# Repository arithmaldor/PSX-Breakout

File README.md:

# Copyright and Disclaimer
Copyright: Jacob Proctor

This documentation describes Open Hardware and is licensed under the
CERN OHL v. 1.2.

You may redistribute and modify this documentation under the terms of the
CERN OHL v.1.2. (http://ohwr.org/cernohl). This documentation is distributed
WITHOUT ANY EXPRESS OR IMPLIED WARRANTY, INCLUDING OF
MERCHANTABILITY, SATISFACTORY QUALITY AND FITNESS FOR A
PARTICULAR PURPOSE. Please see the CERN OHL v.1.2 for applicable
conditions

# PSX Breakout
Breaks out all of the signals from the PSX AV out so you can easily access them. 

# Operation
Plug in and go.

## HD15 SYNC Selector 
Located on the back left of the board, this switch determines which signal goes to the HD15 port - CVBS or LUMA.

# Parts
Refer to BOM.csv for all components. For the support leg, use any appropriately long brass/metal m3 standoff/pillar and screw a rubber foot to the bottom. Solder a 5mm spring clamp to the bottom of the board to adjust the height.
For the phat PS3, standoffs may need to be screwed into each other (stacked) to reach the needed height.

# Case
The incredible [Magic Trashman](https://twitter.com/MagicTrashman) was kind enough to design 3D printable cases for both my Nintendo and PSX breakouts. They are under the same license as the PCB and are free to use, but if you order through thingiverse you can leave him a nice tip. Current designs fit the height of the original PS1 and the original SNES, but can be easily adjusted for height if you have some basic 3D design skills. They are held together with 2x 14mm M3 machine screws.
Pictures: https://t.co/ojJ8epfZXH?amp=1
Thingiverse: https://t.co/7dF171BqaF?amp=1
Bonus: If you plug the Nintendo/Sony connector into the console and screw the PCB into the bottom of the case, it makes it a lot easier to solder the connector to the board as it is held in place.

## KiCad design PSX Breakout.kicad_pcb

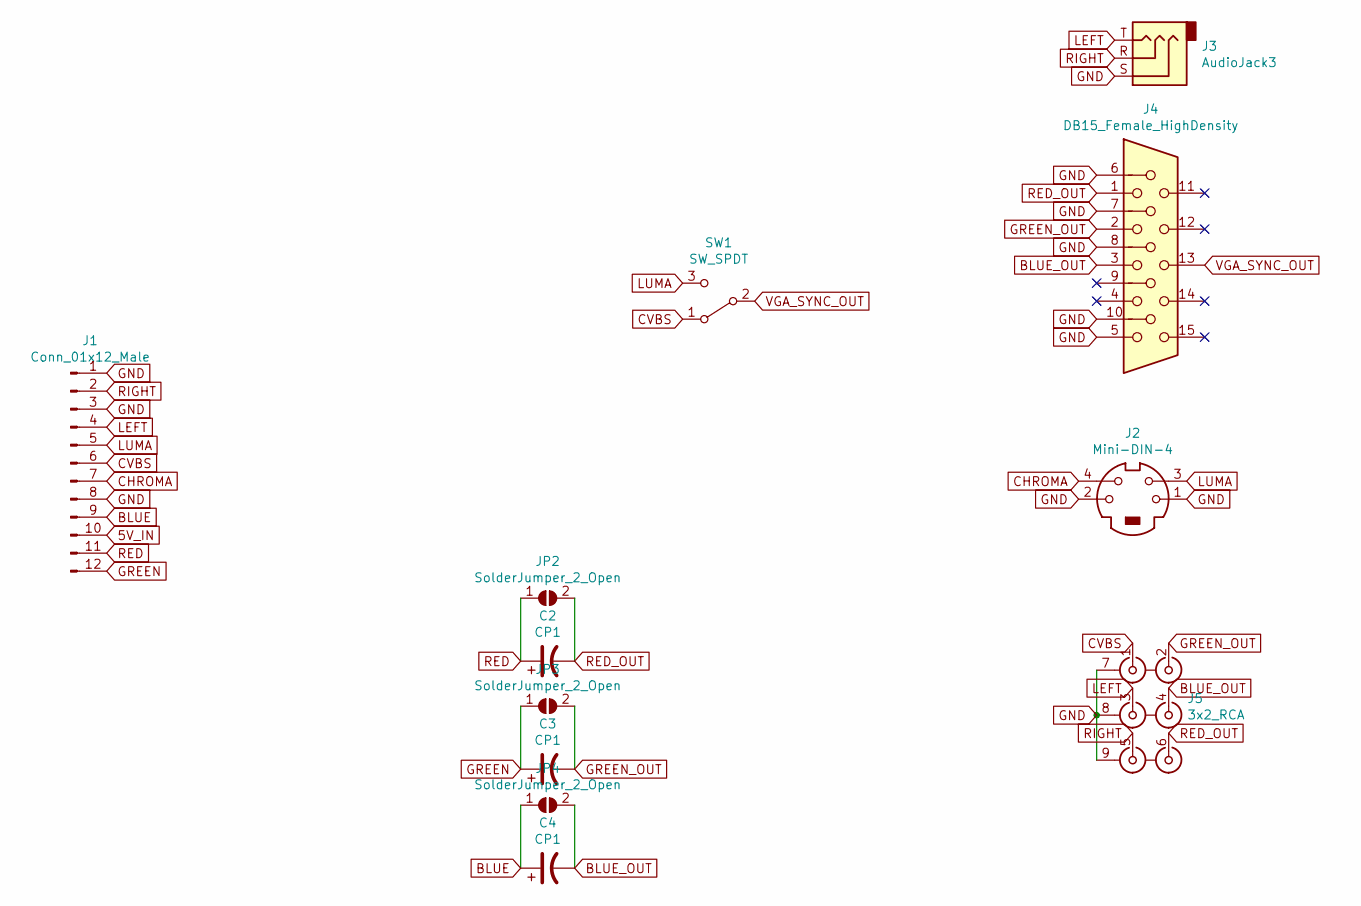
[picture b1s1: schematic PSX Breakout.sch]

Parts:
C2, C3, C4: CP1; CP_Elec_10x10
J1: Conn_01x12_Male; PSX_AV
J2: Mini-DIN-4; CUI_MD-40SG
J3: AudioJack3; CUI_SJ1-3533NG
J4: DB15_Female_HighDensity; VGA
J5: 3x2_RCA
JP2, JP3, JP4: SolderJumper_2_Open; SolderJumper-2_P1.3mm_Open_TrianglePad1.0x1.5mm
SW1: SW_SPDT; C&K_SPDT

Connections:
5V_IN: J1.10
BLUE: C4.1, J1.9, JP4.1 (A)
BLUE_OUT: C4.2, J4.3, J5.4 (INGRN), JP4.2 (B)
CHROMA: J1.7, J2.4
CVBS: J1.6, J5.1 (INSYN), SW1.1 (A)
GND: J1.1, J1.3, J1.8, J2.1, J2.2, J3.S, J4.0, J4.5, J4.6, J4.7, J4.8, J4.10, J5.7 (GND), J5.8 (GND), J5.9 (GND), SW1.S
GREEN: C3.1, J1.12, JP3.1 (A)
GREEN_OUT: C3.2, J4.2, J5.2 (INRED), JP3.2 (B)
LEFT: J1.4, J3.T, J5.3 (INLAU)
LUMA: J1.5, J2.3, SW1.3 (C)
RED: C2.1, J1.11, JP2.1 (A)
RED_OUT: C2.2, J4.1, J5.6 (INBLU), JP2.2 (B)
RIGHT: J1.2, J3.R, J5.5 (INRAU)
VGA_SYNC_OUT: J4.13, SW1.2 (B)

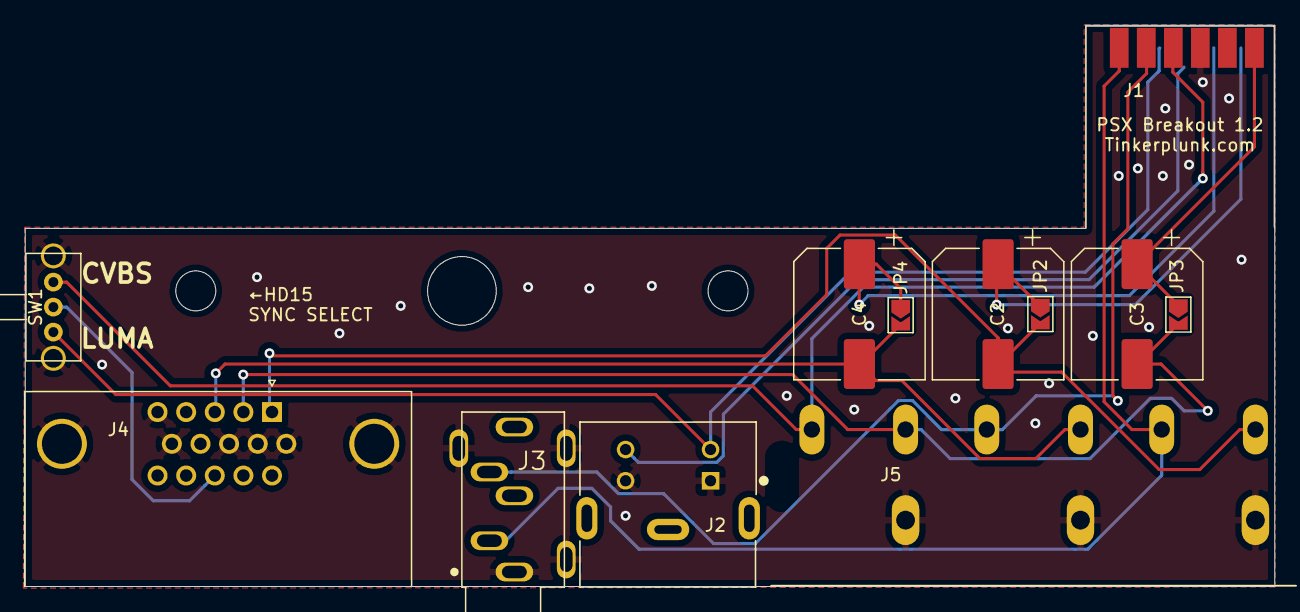
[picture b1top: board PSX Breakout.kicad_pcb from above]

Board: 2 copper layers, 100.0 x 44.9 mm, 12 parts (0 on the bottom side), 13 nets.

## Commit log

2019-06-09 Updated Case Gerbers
2019-06-09 Case edit, renders
    moved the case back a bit behind the RCA jacks to give space, added renders that include the case.
2019-06-11 Fixing Merging Error
    Updated Case, moved connector, generated gerbers
2019-06-13 Changed headphone jack footprint
    Added pins to the headphone jack footprint so it is compatible with all SJ1-353x-n, ng, and ns series jacks.
2019-06-13 Completed BOM
2019-06-16 Big Changes
    Moved the csync selector switch to the right in order to move the hd15 connector back to the right position. Fixed hd15 footprint, moved screw holes and updated case with new screw holes and input la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
2019-06-17 Updated BOM
2019-06-17 Fixed Gerbers, added footprints
    Updated gerbers, and added all footprints used on this board to the PSX_BREAKOUT.Pretty folder.
2019-06-18 Added Hardware BOM
    Added hardware BOM and diagram, updated readme.
2019-06-25 Fixed s-video and headphone footprint, added support hole
2019-07-03 no change
2019-07-06 Updated to 1.2
    Removed sync stripper, shrunk board, added switch to select sync source of HD15 port only.
2019-07-31 Changed s-video footprint
2019-07-31 Update fp-info-cache
2019-08-02 Finishing Touches
2019-09-09 Add links for case files

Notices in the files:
PSX Breakout.kicad_pcb:
Licensed under CERN OHL 1.2
